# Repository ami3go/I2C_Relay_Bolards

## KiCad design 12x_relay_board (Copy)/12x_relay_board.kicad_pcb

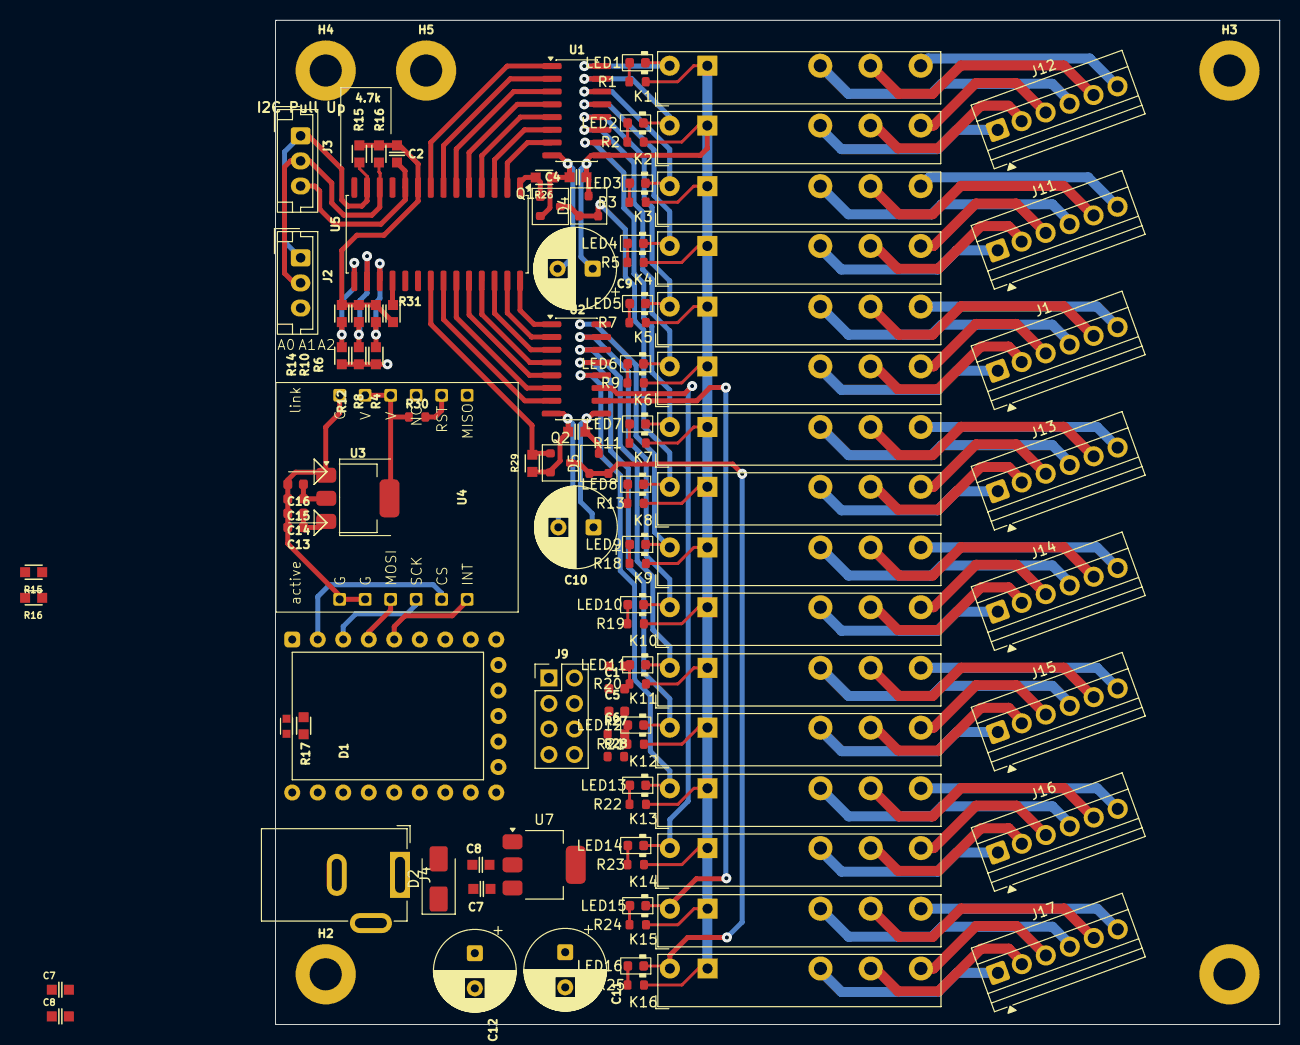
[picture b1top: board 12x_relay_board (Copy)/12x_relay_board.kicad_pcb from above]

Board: 2 copper layers, 100.0 x 100.0 mm, 113 parts (0 on the bottom side), 125 nets.

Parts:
C1, C5, C6, C14, C15: 100nF; C_0603
C2, C3, C4, C7, C7#2, C8, C8#2: 100nF_0603_16V; C_0603
C9, C10, C11, C12: 470uF_25V; CP_Radial_D8.0mm_P3.50mm
C13, C16: 1uF; C_0603
D1: LED_0603
D2: SS14; D_SMA
D4, D5: BAV23C; SOT-23
H1, H2, H3, H4, H5: MountingHole_M3_3.2mm_Pad; MountingHole_3.2mm_Pad
J1, J11, J12, J13, J14, J15, J16, J17: Conn_01x06_Pin; TerminalBlock_Xinya_XY308-2.54-6P_1x06_P2.54mm_Horizontal
J2, J3: JST_03; JST_EH_B3B-EH-A_1x03_P2.50mm_Vertical
J4: Barrel_Jack_Switch; BarrelJack_GCT_DCJ200-10-A_Horizontal
J9: Conn_01x08; PinHeader_2x04_P2.54mm_Vertical
K1, K2, K3, K4, K5, K6, K7, K8, K9, K10, K11, K12, K13, K14, K15, K16: FINDER-34.51; Relay_SPDT_Finder_34.51_Vertical
LED1, LED2, LED3, LED4, LED5, LED6, LED7, LED8, LED9, LED10, LED11, LED12, LED13, LED14, LED15, LED16: LED_0603; LED_0603_1608Metric
Q1, Q2: 2N7002; SOT-23
R1, R2, R3, R5, R7, R9, R11, R13, R18, R19, R20, R21, R22, R23, R24, R25, R27, R28: 4.7kΩ; R_0603
R4, R6, R8, R10, R12, R14, R17, R31: 1k_0603; R_0603
R15, R15#2, R16, R16#2, R26, R29: 10k_0603; R_0603
R30: 10kΩ; R_0603
RZ2: RP2040-Zero; RP2040-Zero_socket
U1, U2: ULN2003; SOIC-16_3.9x9.9mm_P1.27mm
U3, U7: LM1117MP-3.3; SOT-223-3_TabPin2
U4: ENC28J60MODULE; W5500Lite-module
U5: MCP23017_SO; SOIC-28W_7.5x17.9mm_P1.27mm

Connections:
+3V3: C1.1, C6.1, J9.3, R15#2.1, R16.1, R27.1, R28.1, RZ2.21 (3V3)
+5V: C5.1, C13.1, C14.1, J9.2, RZ2.23 (+5V), U3.3 (VI)
/ETH/INT: RZ2.5 (GP4), U4.7 (INT)
/ETH/RST: R30.2, U4.5 (RST)
/Relay_driver1/IN1: U2.1 (I1), U5.28 (GPA7)
/Relay_driver1/IN2: U2.2 (I2), U5.27 (GPA6)
/Relay_driver1/IN3: U2.3 (I3), U5.26 (GPA5)
/Relay_driver1/IN4: U2.4 (I4), U5.25 (GPA4)
/Relay_driver1/IN5: U2.5 (I5), U5.24 (GPA3)
/Relay_driver1/IN6: U2.6 (I6), U5.23 (GPA2)
/Relay_driver1/IN7: U2.7 (I7), U5.22 (GPA1)
/Relay_driver1/IN8: Q2.1 (G), R29.1, U5.21 (GPA0)
/Relay_driver1/OUT1: K9.A2, LED9.1 (K), U2.16 (O1)
/Relay_driver1/OUT2: K10.A2, LED10.1 (K), U2.15 (O2)
/Relay_driver1/OUT3: K11.A2, LED11.1 (K), U2.14 (O3)
/Relay_driver1/OUT4: K12.A2, LED12.1 (K), U2.13 (O4)
/Relay_driver1/OUT5: K13.A2, LED13.1 (K), U2.12 (O5)
/Relay_driver1/OUT6: K14.A2, LED14.1 (K), U2.11 (O6)
/Relay_driver1/OUT7: K15.A2, LED15.1 (K), U2.10 (O7)
/Relay_driver1/OUT8: D5.1 (A2), D5.2 (A1), K16.A2, LED16.1 (K), Q2.3 (D)
/Relay_driver/IN1: U1.1 (I1), U5.8 (GPB7)
/Relay_driver/IN2: U1.2 (I2), U5.7 (GPB6)
/Relay_driver/IN3: U1.3 (I3), U5.6 (GPB5)
/Relay_driver/IN4: U1.4 (I4), U5.5 (GPB4)
/Relay_driver/IN5: U1.5 (I5), U5.4 (GPB3)
/Relay_driver/IN6: U1.6 (I6), U5.3 (GPB2)
/Relay_driver/IN7: U1.7 (I7), U5.2 (GPB1)
/Relay_driver/IN8: Q1.1 (G), R26.1, U5.1 (GPB0)
/Relay_driver/OUT1: K1.A2, LED1.1 (K), U1.16 (O1)
/Relay_driver/OUT2: K2.A2, LED2.1 (K), U1.15 (O2)
/Relay_driver/OUT3: K3.A2, LED3.1 (K), U1.14 (O3)
/Relay_driver/OUT4: K4.A2, LED4.1 (K), U1.13 (O4)
/Relay_driver/OUT5: K5.A2, LED5.1 (K), U1.12 (O5)
/Relay_driver/OUT6: K6.A2, LED6.1 (K), U1.11 (O6)
/Relay_driver/OUT7: K7.A2, LED7.1 (K), U1.10 (O7)
/Relay_driver/OUT8: D4.1 (A2), D4.2 (A1), K8.A2, LED8.1 (K), Q1.3 (D)
/Two_relays_1/Relay_channel_1/COM: J12.5, K1.11
/Two_relays_1/Relay_channel_1/NC: J12.4, K1.12
/Two_relays_1/Relay_channel_1/NO: J12.6, K1.14
/Two_relays_1/Relay_channel_2/COM: J12.2, K2.11
/Two_relays_1/Relay_channel_2/NC: J12.1, K2.12
/Two_relays_1/Relay_channel_2/NO: J12.3, K2.14
/Two_relays_2/Relay_channel_1/COM: J11.5, K3.11
/Two_relays_2/Relay_channel_1/NC: J11.4, K3.12
/Two_relays_2/Relay_channel_1/NO: J11.6, K3.14
/Two_relays_2/Relay_channel_2/COM: J11.2, K4.11
/Two_relays_2/Relay_channel_2/NC: J11.1, K4.12
/Two_relays_2/Relay_channel_2/NO: J11.3, K4.14
/Two_relays_3/Relay_channel_1/COM: J1.5, K5.11
/Two_relays_3/Relay_channel_1/NC: J1.4, K5.12
/Two_relays_3/Relay_channel_1/NO: J1.6, K5.14
/Two_relays_3/Relay_channel_2/COM: J1.2, K6.11
/Two_relays_3/Relay_channel_2/NC: J1.1, K6.12
/Two_relays_3/Relay_channel_2/NO: J1.3, K6.14
/Two_relays_4/Relay_channel_1/COM: J13.5, K7.11
/Two_relays_4/Relay_channel_1/NC: J13.4, K7.12
/Two_relays_4/Relay_channel_1/NO: J13.6, K7.14
/Two_relays_4/Relay_channel_2/COM: J13.2, K8.11
/Two_relays_4/Relay_channel_2/NC: J13.1, K8.12
/Two_relays_4/Relay_channel_2/NO: J13.3, K8.14
/Two_relays_5/Relay_channel_1/COM: J14.5, K9.11
/Two_relays_5/Relay_channel_1/NC: J14.4, K9.12
/Two_relays_5/Relay_channel_1/NO: J14.6, K9.14
/Two_relays_5/Relay_channel_2/COM: J14.2, K10.11
/Two_relays_5/Relay_channel_2/NC: J14.1, K10.12
/Two_relays_5/Relay_channel_2/NO: J14.3, K10.14
/Two_relays_6/Relay_channel_1/COM: J15.5, K11.11
/Two_relays_6/Relay_channel_1/NC: J15.4, K11.12
/Two_relays_6/Relay_channel_1/NO: J15.6, K11.14
/Two_relays_6/Relay_channel_2/COM: J15.2, K12.11
/Two_relays_6/Relay_channel_2/NC: J15.1, K12.12
/Two_relays_6/Relay_channel_2/NO: J15.3, K12.14
/Two_relays_7/Relay_channel_1/COM: J16.5, K13.11
/Two_relays_7/Relay_channel_1/NC: J16.4, K13.12
/Two_relays_7/Relay_channel_1/NO: J16.6, K13.14
/Two_relays_7/Relay_channel_2/COM: J16.2, K14.11
/Two_relays_7/Relay_channel_2/NC: J16.1, K14.12
/Two_relays_7/Relay_channel_2/NO: J16.3, K14.14
/Two_relays_8/Relay_channel_1/COM: J17.5, K15.11
/Two_relays_8/Relay_channel_1/NC: J17.4, K15.12
/Two_relays_8/Relay_channel_1/NO: J17.6, K15.14
/Two_relays_8/Relay_channel_2/COM: J17.2, K16.11
/Two_relays_8/Relay_channel_2/NC: J17.1, K16.12
/Two_relays_8/Relay_channel_2/NO: J17.3, K16.14
/Untitled Sheet/I2C0_SCL: R16.2, RZ2.14 (GP13)
/Untitled Sheet/I2C0_SDA: R15#2.2, RZ2.13 (GP12)
/Untitled Sheet/I2C1_SCL: J9.5, R27.2, RZ2.18 (GP27)
/Untitled Sheet/I2C1_SDA: J9.7, R28.2, RZ2.17 (GP26)
/Untitled Sheet/SPI0_CS: RZ2.2 (GP1), U4.8 (CS)
/Untitled Sheet/SPI0_MOSI: RZ2.4 (GP3), U4.10 (MOSI)
/Untitled Sheet/SPI0_RX: RZ2.1 (GP0), U4.6 (MISO)
/Untitled Sheet/SPI0_SCK: RZ2.3 (GP2), U4.9 (SCK)
/conrol/PWR_VDD: C2.1, R4.1, R8.1, R12.1, R31.1, U5.9 (VDD)
/conrol/SCL: J2.2, J3.2, R16#2.2, U5.12 (SCK)
/conrol/SDA: J2.1, J3.1, R15.2, U5.13 (SDA)
GND: C1.2, C5.2, C6.2, C13.2, C14.2, C15.2, C16.2, J9.1, J9.8, RZ2.22 (GND), U3.1 (GND), U4.1 (G), U4.11 (GND), U4.12 (GND)
unnamed: D1.2 (A), R17.2
unnamed: D2.2 (A), J4.1
unnamed: J9.4, RZ2.20 (GP29)
unnamed: J9.6, RZ2.19 (GP28)
unnamed: LED1.2 (A), R1.2
unnamed: LED2.2 (A), R2.2
unnamed: LED3.2 (A), R3.2
unnamed: LED4.2 (A), R5.2
unnamed: LED5.2 (A), R7.2
unnamed: LED6.2 (A), R9.2
unnamed: LED7.2 (A), R11.2
unnamed: LED8.2 (A), R13.2
unnamed: LED9.2 (A), R18.2
unnamed: LED10.2 (A), R19.2
unnamed: LED11.2 (A), R20.2
unnamed: LED12.2 (A), R21.2
unnamed: LED13.2 (A), R22.2
unnamed: LED14.2 (A), R23.2
unnamed: LED15.2 (A), R24.2
unnamed: LED16.2 (A), R25.2
unnamed: C15.1, C16.1, R30.1, U3.2 (VO), U4.2 (P3V3), U4.3 (P3V3)
unnamed: R12.2, R14.1, U5.15 (A0)
unnamed: R8.2, R10.1, U5.16 (A1)
unnamed: R4.2, R6.1, U5.17 (A2)
unnamed: R31.2, U5.18 (~RESET)
PWR_3V3: C8.1, U7.2 (VO)
PWR_5V: C8#2.1, R15.1, R16#2.1
PWR_12V: C3.1, C4.1, C7.1, C7#2.1, C9.1, C10.1, C11.1, C12.1, D2.1 (K), D4.3 (K), D5.3 (K), K1.A1, K2.A1, K3.A1, K4.A1, K5.A1, K6.A1, K7.A1, K8.A1, K9.A1, K10.A1, K11.A1, K12.A1, K13.A1, K14.A1, K15.A1, K16.A1, R1.1, R2.1, R3.1, R5.1, R7.1, R9.1, R11.1, R13.1, R17.1, R18.1, R19.1, R20.1, R21.1, R22.1, R23.1, R24.1, R25.1, U1.9 (COM), U2.9 (COM), U7.3 (VI)
PWR_GND: C2.2, C3.2, C4.2, C7.2, C7#2.2, C8.2, C8#2.2, C9.2, C10.2, C11.2, C12.2, D1.1 (K), J2.3, J3.3, J4.2, J4.3, Q1.2 (S), Q2.2 (S), R6.2, R10.2, R14.2, R26.2, R29.2, U1.8 (GND), U2.8 (GND), U5.10 (VSS), U7.1 (GND)

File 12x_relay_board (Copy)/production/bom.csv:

Designator,Footprint,Quantity,Value,LCSC Part #
"C10, C11, C12, C9",CP_Radial_D8.0mm_P3.50mm,4,470uF_25V,
"C2, C3, C4, C7, C8",C_0603,5,100nF_0603_16V,
D1,LED_0603,1,LED_0603,
D2,D_SMA,1,SS14,
"H1, H2, H3, H4, H5",MountingHole_3.2mm_Pad,5,MountingHole_M3_3.2mm_Pad,
J1,PinHeader_1x36_P2.54mm_Vertical,1,Conn_01x36_MountingPin,
"J2, J3",JST_EH_B3B-EH-A_1x03_P2.50mm_Vertical,2,JST_03,
J4,BarrelJack_GCT_DCJ200-10-A_Horizontal,1,Barrel_Jack_Switch,
"K1, K10, K11, K12, K2, K3, K4, K5, K6, K7, K8, K9",Relay_SPDT_Finder_34.51_Vertical,12,FINDER-34.51,
"R10, R12, R14, R17, R2, R4, R6, R8",R_0603,8,1k_0603,
"R15, R16",R_0603,2,10k_0603,
"U1, U2",SOIC-16_3.9x9.9mm_P1.27mm,2,ULN2003,
U5,SOIC-28W_7.5x17.9mm_P1.27mm,1,MCP23017_SO,
U7,SOT-223-3_TabPin2,1,LM1117MP-3.3,

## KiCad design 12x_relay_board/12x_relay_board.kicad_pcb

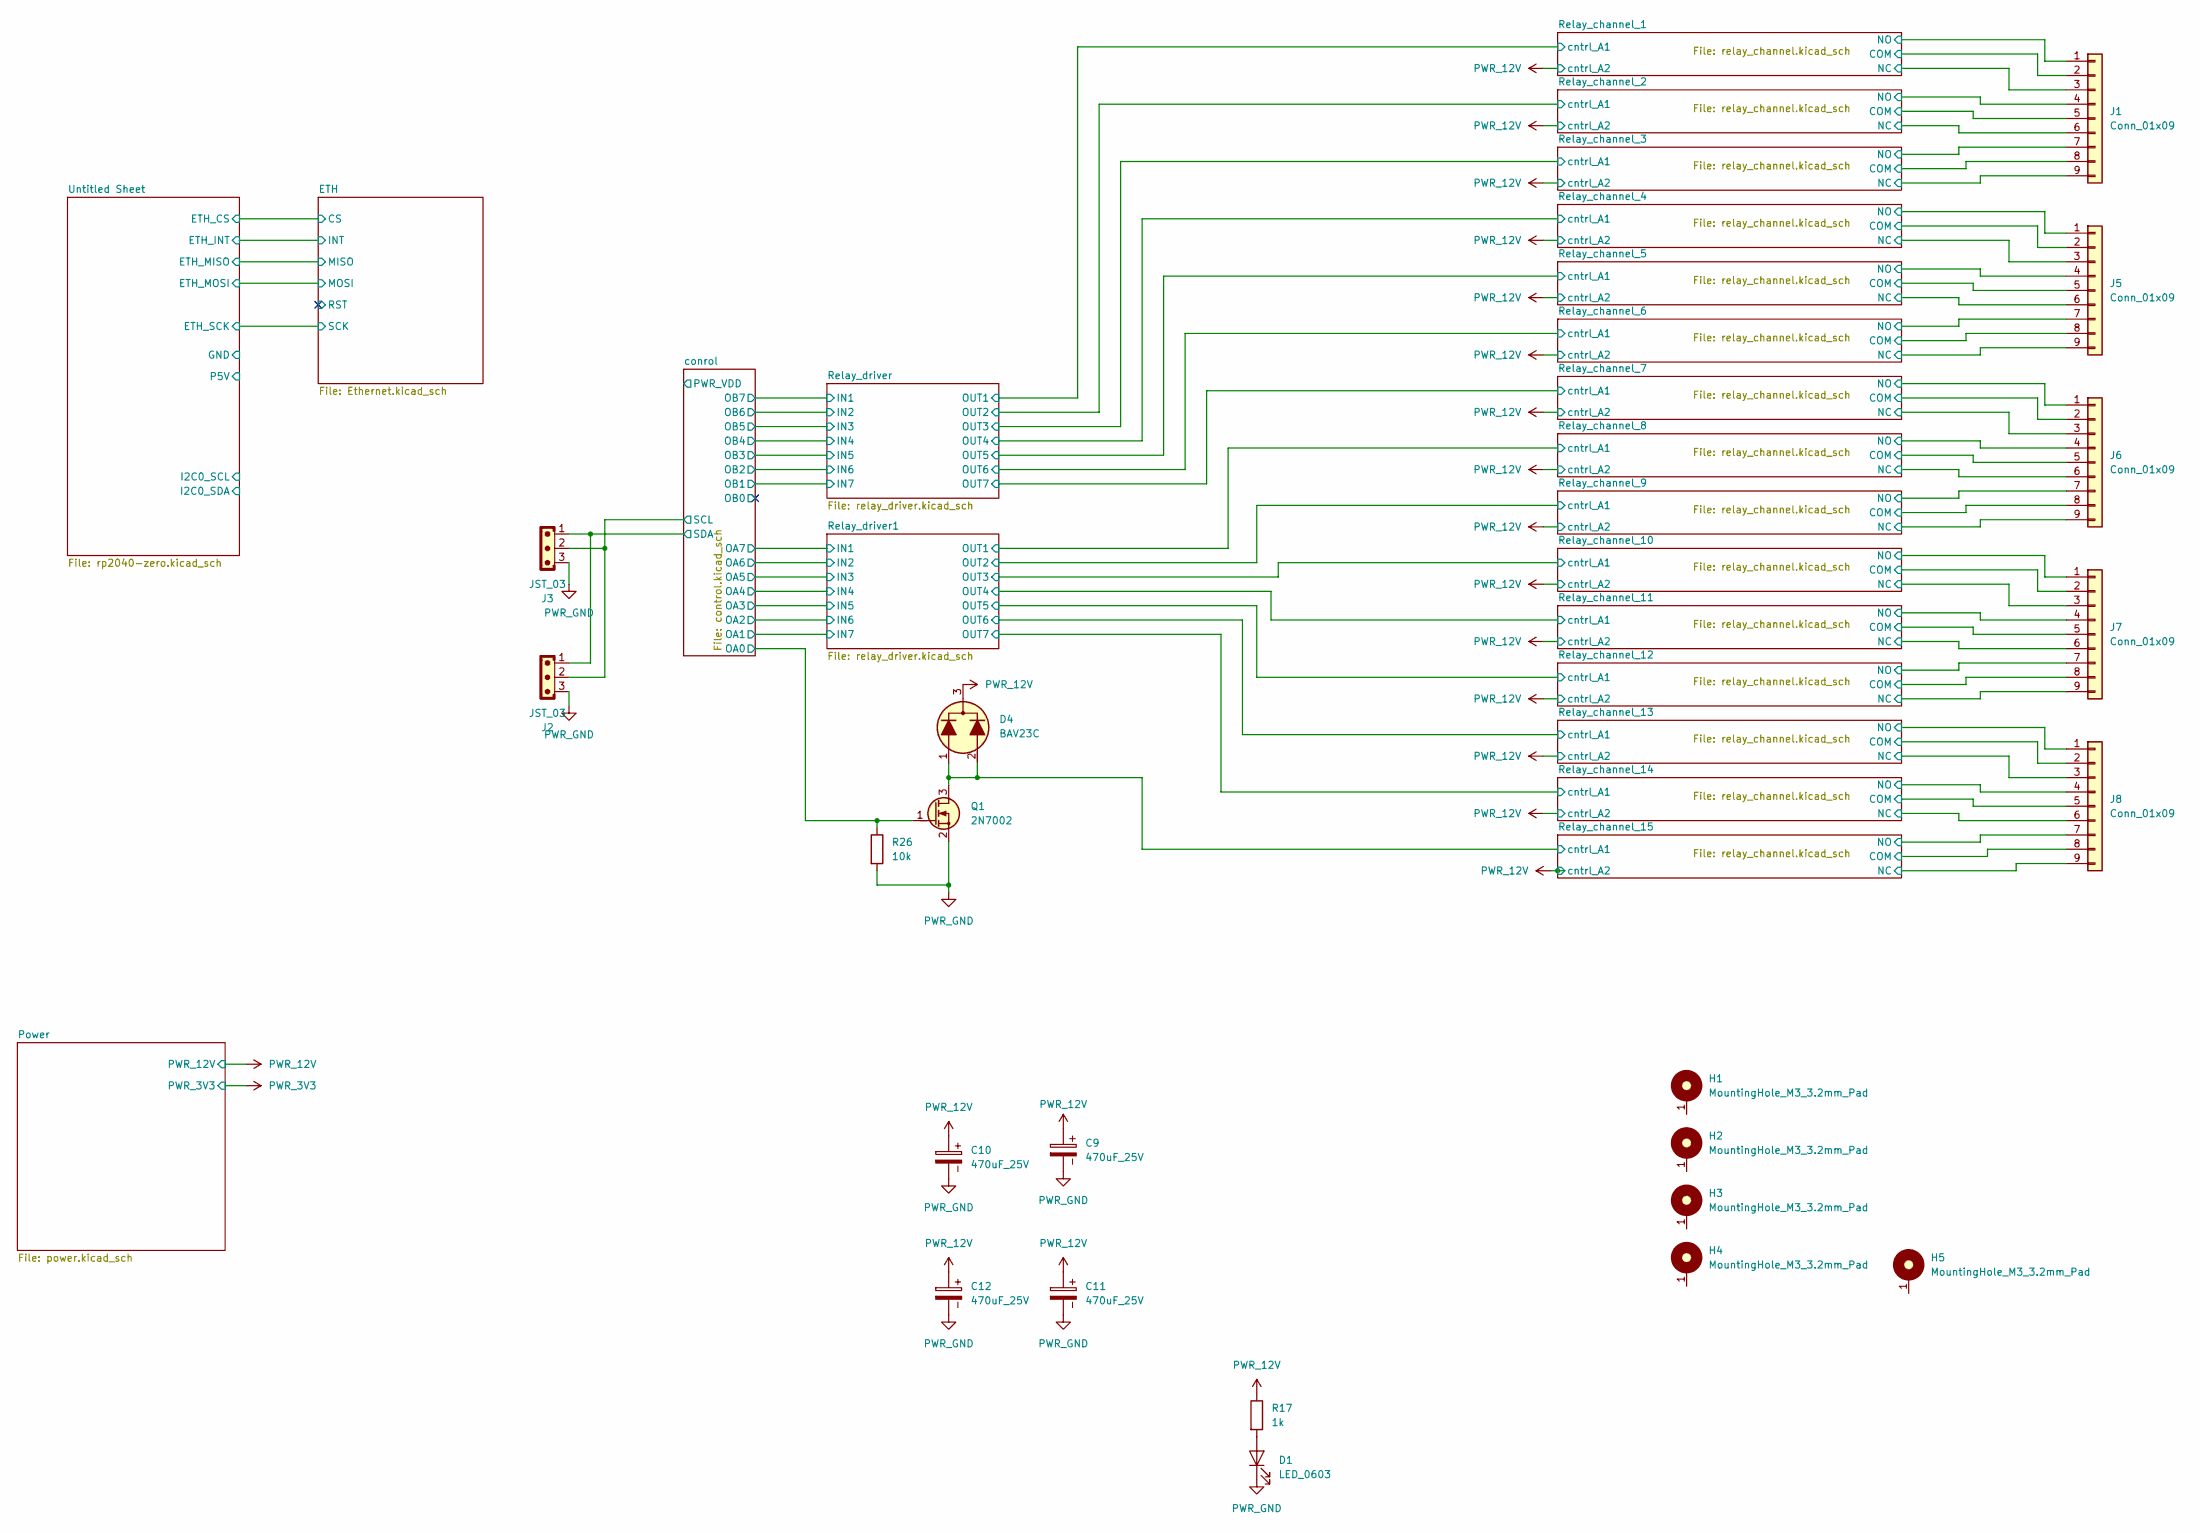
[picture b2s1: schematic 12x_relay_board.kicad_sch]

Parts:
C9, C10, C11, C12: 470uF_25V; CP_Radial_D8.0mm_P3.50mm
D1: LED_0603
D4: BAV23C; SOT-23
H1, H2, H3, H4, H5: MountingHole_M3_3.2mm_Pad; MountingHole_3.2mm_Pad
J1, J5, J6, J7, J8: Conn_01x09; TerminalBlock_Xinya_XY308-2.54-9P_1x09_P2.54mm_Horizontal
J2, J3: JST_03; JST_EH_B3B-EH-A_1x03_P2.50mm_Vertical
Q1: 2N7002; SOT-23
R17: 1k_0603; R_0603; Part Number RC0603FR-071KL; JLCPCB ID C21190
R26: 10k_0603; R_0603; Part Number RC0603FR-0710KL; JLCPCB ID C25804

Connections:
/Relay_channel_1/COM: J1.2; also elsewhere on the board
/Relay_channel_1/NC: J1.3; also elsewhere on the board
/Relay_channel_1/NO: J1.1; also elsewhere on the board
/Relay_channel_2/COM: J1.5; also elsewhere on the board
/Relay_channel_2/NC: J1.6; also elsewhere on the board
/Relay_channel_2/NO: J1.4; also elsewhere on the board
/Relay_channel_3/COM: J1.8; also elsewhere on the board
/Relay_channel_3/NC: J1.9; also elsewhere on the board
/Relay_channel_3/NO: J1.7; also elsewhere on the board
/Relay_channel_4/COM: J5.2; also elsewhere on the board
/Relay_channel_4/NC: J5.3; also elsewhere on the board
/Relay_channel_4/NO: J5.1; also elsewhere on the board
/Relay_channel_5/COM: J5.5; also elsewhere on the board
/Relay_channel_5/NC: J5.6; also elsewhere on the board
/Relay_channel_5/NO: J5.4; also elsewhere on the board
/Relay_channel_6/COM: J5.8; also elsewhere on the board
/Relay_channel_6/NC: J5.9; also elsewhere on the board
/Relay_channel_6/NO: J5.7; also elsewhere on the board
/Relay_channel_7/COM: J6.2; also elsewhere on the board
/Relay_channel_7/NC: J6.3; also elsewhere on the board
/Relay_channel_7/NO: J6.1; also elsewhere on the board
/Relay_channel_8/COM: J6.5; also elsewhere on the board
/Relay_channel_8/NC: J6.6; also elsewhere on the board
/Relay_channel_8/NO: J6.4; also elsewhere on the board
/Relay_channel_9/COM: J6.8; also elsewhere on the board
/Relay_channel_9/NC: J6.9; also elsewhere on the board
/Relay_channel_9/NO: J6.7; also elsewhere on the board
/Relay_channel_10/COM: J7.2; also elsewhere on the board
/Relay_channel_10/NC: J7.3; also elsewhere on the board
/Relay_channel_10/NO: J7.1; also elsewhere on the board
/Relay_channel_11/COM: J7.5; also elsewhere on the board
/Relay_channel_11/NC: J7.6; also elsewhere on the board
/Relay_channel_11/NO: J7.4; also elsewhere on the board
/Relay_channel_12/COM: J7.8; also elsewhere on the board
/Relay_channel_12/NC: J7.9; also elsewhere on the board
/Relay_channel_12/NO: J7.7; also elsewhere on the board
/Relay_channel_13/COM: J8.2; also elsewhere on the board
/Relay_channel_13/NC: J8.3; also elsewhere on the board
/Relay_channel_13/NO: J8.1; also elsewhere on the board
/Relay_channel_14/COM: J8.5; also elsewhere on the board
/Relay_channel_14/NC: J8.6; also elsewhere on the board
/Relay_channel_14/NO: J8.4; also elsewhere on the board
/Relay_channel_15/COM: J8.8; also elsewhere on the board
/Relay_channel_15/NC: J8.9; also elsewhere on the board
/Relay_channel_15/NO: J8.7; also elsewhere on the board
/Relay_channel_15/cntrl_A1: D4.1 (A2), D4.2 (A1), Q1.3 (D); also elsewhere on the board
/conrol/OA0: Q1.1 (G), R26.1; also elsewhere on the board
/conrol/SCL: J2.2, J3.2; also elsewhere on the board
/conrol/SDA: J2.1, J3.1; also elsewhere on the board
unnamed: D1.2 (A), R17.2
PWR_12V: C9.1, C10.1, C11.1, C12.1, D4.3 (K), R17.1; also elsewhere on the board
PWR_GND: C9.2, C10.2, C11.2, C12.2, D1.1 (K), J2.3, J3.3, Q1.2 (S), R26.2; also elsewhere on the board

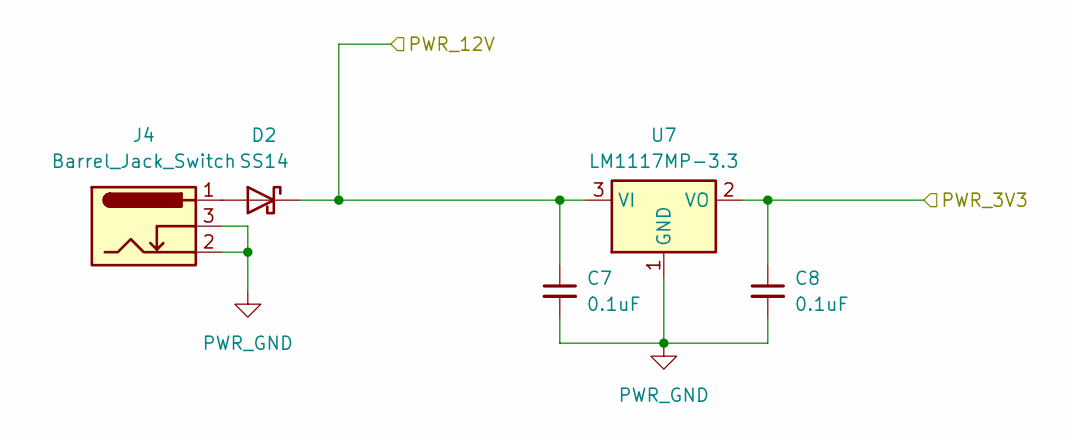
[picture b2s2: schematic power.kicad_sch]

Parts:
C7, C8: 100nF_0603_16V; C_0603; Part Number 0603YC104KAT2A; JLCPCB ID C14663
D2: SS14; D_SMA
J4: Barrel_Jack_Switch; BarrelJack_GCT_DCJ200-10-A_Horizontal
U7: LM1117MP-3.3; SOT-223-3_TabPin2

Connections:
unnamed: D2.2 (A), J4.1
PWR_12V: C7.1, D2.1 (K), U7.3 (VI); also elsewhere on the board
PWR_GND: C7.2, C8.2, J4.2, J4.3, U7.1 (GND); also elsewhere on the board

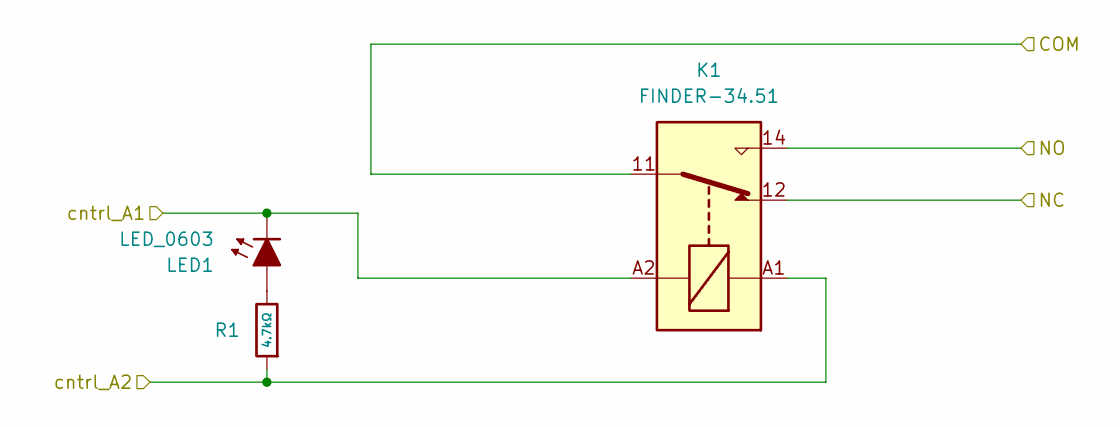
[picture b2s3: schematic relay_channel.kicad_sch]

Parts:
K1: FINDER-34.51; Relay_SPDT_Finder_34.51_Vertical
LED1: LED_0603; LED_0603_1608Metric
R1: 4.7kΩ; R_0603; Overload Voltage (Max) 75V; Tolerance ±1%; Part 0603WAF4701T5E; LCSC C23162

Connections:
/Relay_channel_1/COM: K1.11; also elsewhere on the board
/Relay_channel_1/NC: K1.12; also elsewhere on the board
/Relay_channel_1/NO: K1.14; also elsewhere on the board
/Relay_channel_1/cntrl_A1: K1.A2, LED1.1 (K); also elsewhere on the board
unnamed: LED1.2 (A), R1.2
PWR_12V: K1.A1, R1.1; also elsewhere on the board

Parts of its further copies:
K2, K3, K4, K5, K6, K7, K8, K9, K10, K11, K12, K13, K14, K15: FINDER-34.51; Relay_SPDT_Finder_34.51_Vertical
LED2, LED3, LED4, LED5, LED6, LED7, LED8, LED9, LED10, LED11, LED12, LED13, LED14, LED15: LED_0603; LED_0603_1608Metric
R3, R5, R7, R9, R11, R13, R18, R19, R20, R21, R22, R23, R24, R25: 4.7kΩ; R_0603; Overload Voltage (Max) 75V; Tolerance ±1%; Part 0603WAF4701T5E; LCSC C23162

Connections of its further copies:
/Relay_channel_2/COM: K2.11; also elsewhere on the board
/Relay_channel_2/NC: K2.12; also elsewhere on the board
/Relay_channel_2/NO: K2.14; also elsewhere on the board
/Relay_channel_2/cntrl_A1: K2.A2, LED2.1 (K); also elsewhere on the board
/Relay_channel_3/COM: K3.11; also elsewhere on the board
/Relay_channel_3/NC: K3.12; also elsewhere on the board
/Relay_channel_3/NO: K3.14; also elsewhere on the board
/Relay_channel_3/cntrl_A1: K3.A2, LED3.1 (K); also elsewhere on the board
/Relay_channel_4/COM: K4.11; also elsewhere on the board
/Relay_channel_4/NC: K4.12; also elsewhere on the board
/Relay_channel_4/NO: K4.14; also elsewhere on the board
/Relay_channel_4/cntrl_A1: K4.A2, LED4.1 (K); also elsewhere on the board
/Relay_channel_5/COM: K5.11; also elsewhere on the board
/Relay_channel_5/NC: K5.12; also elsewhere on the board
/Relay_channel_5/NO: K5.14; also elsewhere on the board
/Relay_channel_5/cntrl_A1: K5.A2, LED5.1 (K); also elsewhere on the board
/Relay_channel_6/COM: K6.11; also elsewhere on the board
/Relay_channel_6/NC: K6.12; also elsewhere on the board
/Relay_channel_6/NO: K6.14; also elsewhere on the board
/Relay_channel_6/cntrl_A1: K6.A2, LED6.1 (K); also elsewhere on the board
/Relay_channel_7/COM: K7.11; also elsewhere on the board
/Relay_channel_7/NC: K7.12; also elsewhere on the board
/Relay_channel_7/NO: K7.14; also elsewhere on the board
/Relay_channel_7/cntrl_A1: K7.A2, LED7.1 (K); also elsewhere on the board
/Relay_channel_8/COM: K8.11; also elsewhere on the board
/Relay_channel_8/NC: K8.12; also elsewhere on the board
/Relay_channel_8/NO: K8.14; also elsewhere on the board
/Relay_channel_8/cntrl_A1: K8.A2, LED8.1 (K); also elsewhere on the board
/Relay_channel_9/COM: K9.11; also elsewhere on the board
/Relay_channel_9/NC: K9.12; also elsewhere on the board
/Relay_channel_9/NO: K9.14; also elsewhere on the board
/Relay_channel_9/cntrl_A1: K9.A2, LED9.1 (K); also elsewhere on the board
/Relay_channel_10/COM: K10.11; also elsewhere on the board
/Relay_channel_10/NC: K10.12; also elsewhere on the board
/Relay_channel_10/NO: K10.14; also elsewhere on the board
/Relay_channel_10/cntrl_A1: K10.A2, LED10.1 (K); also elsewhere on the board
/Relay_channel_11/COM: K11.11; also elsewhere on the board
/Relay_channel_11/NC: K11.12; also elsewhere on the board
/Relay_channel_11/NO: K11.14; also elsewhere on the board
/Relay_channel_11/cntrl_A1: K11.A2, LED11.1 (K); also elsewhere on the board
/Relay_channel_12/COM: K12.11; also elsewhere on the board
/Relay_channel_12/NC: K12.12; also elsewhere on the board
/Relay_channel_12/NO: K12.14; also elsewhere on the board
/Relay_channel_12/cntrl_A1: K12.A2, LED12.1 (K); also elsewhere on the board
/Relay_channel_13/COM: K13.11; also elsewhere on the board
/Relay_channel_13/NC: K13.12; also elsewhere on the board
/Relay_channel_13/NO: K13.14; also elsewhere on the board
/Relay_channel_13/cntrl_A1: K13.A2, LED13.1 (K); also elsewhere on the board
/Relay_channel_14/COM: K14.11; also elsewhere on the board
/Relay_channel_14/NC: K14.12; also elsewhere on the board
/Relay_channel_14/NO: K14.14; also elsewhere on the board
/Relay_channel_14/cntrl_A1: K14.A2, LED14.1 (K); also elsewhere on the board
/Relay_channel_15/COM: K15.11; also elsewhere on the board
/Relay_channel_15/NC: K15.12; also elsewhere on the board
/Relay_channel_15/NO: K15.14; also elsewhere on the board
/Relay_channel_15/cntrl_A1: K15.A2, LED15.1 (K); also elsewhere on the board
unnamed: LED2.2 (A), R3.2
unnamed: LED3.2 (A), R5.2
unnamed: LED4.2 (A), R7.2
unnamed: LED5.2 (A), R9.2
unnamed: LED6.2 (A), R11.2
unnamed: LED7.2 (A), R13.2
unnamed: LED8.2 (A), R18.2
unnamed: LED9.2 (A), R19.2
unnamed: LED10.2 (A), R20.2
unnamed: LED11.2 (A), R21.2
unnamed: LED12.2 (A), R22.2
unnamed: LED13.2 (A), R23.2
unnamed: LED14.2 (A), R24.2
unnamed: LED15.2 (A), R25.2
PWR_12V: K2.A1, K3.A1, K4.A1, K5.A1, K6.A1, K7.A1, K8.A1, K9.A1, K10.A1, K11.A1, K12.A1, K13.A1, K14.A1, K15.A1, R3.1, R5.1, R7.1, R9.1, R11.1, R13.1, R18.1, R19.1, R20.1, R21.1, R22.1, R23.1, R24.1, R25.1; also elsewhere on the board

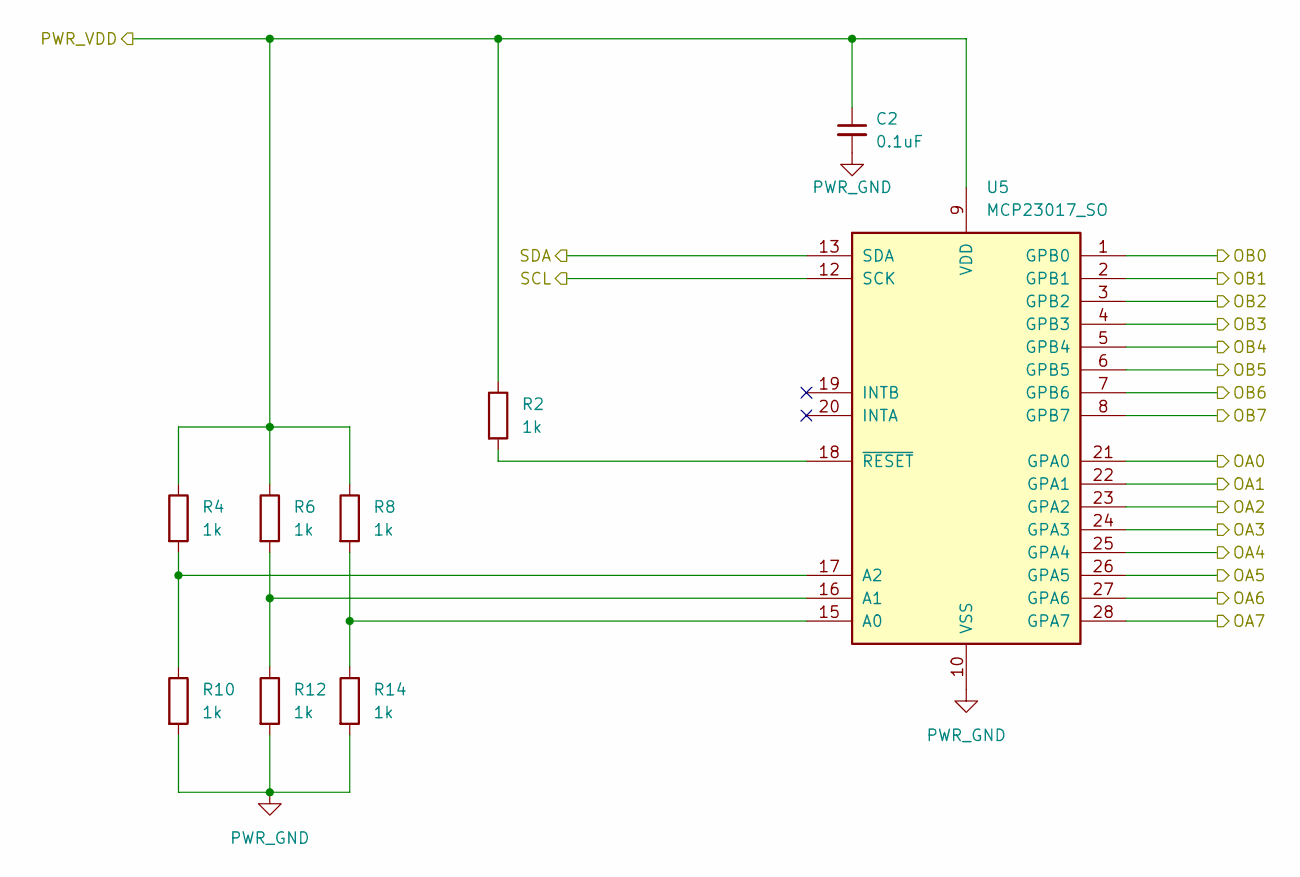
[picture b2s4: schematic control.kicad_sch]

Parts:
C2: 100nF_0603_16V; C_0603; Part Number 0603YC104KAT2A; JLCPCB ID C14663
R2, R4, R6, R8, R10, R12, R14: 1k_0603; R_0603; Part Number RC0603FR-071KL; JLCPCB ID C21190
U5: MCP23017_SO; SOIC-28W_7.5x17.9mm_P1.27mm

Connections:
/Relay_driver1/IN1: U5.28 (GPA7); also elsewhere on the board
/Relay_driver1/IN2: U5.27 (GPA6); also elsewhere on the board
/Relay_driver1/IN3: U5.26 (GPA5); also elsewhere on the board
/Relay_driver1/IN4: U5.25 (GPA4); also elsewhere on the board
/Relay_driver1/IN5: U5.24 (GPA3); also elsewhere on the board
/Relay_driver1/IN6: U5.23 (GPA2); also elsewhere on the board
/Relay_driver1/IN7: U5.22 (GPA1); also elsewhere on the board
/Relay_driver/IN1: U5.8 (GPB7); also elsewhere on the board
/Relay_driver/IN2: U5.7 (GPB6); also elsewhere on the board
/Relay_driver/IN3: U5.6 (GPB5); also elsewhere on the board
/Relay_driver/IN4: U5.5 (GPB4); also elsewhere on the board
/Relay_driver/IN5: U5.4 (GPB3); also elsewhere on the board
/Relay_driver/IN6: U5.3 (GPB2); also elsewhere on the board
/Relay_driver/IN7: U5.2 (GPB1); also elsewhere on the board
/conrol/OA0: U5.21 (GPA0); also elsewhere on the board
/conrol/OB0: U5.1 (GPB0)
/conrol/SCL: U5.12 (SCK); also elsewhere on the board
/conrol/SDA: U5.13 (SDA); also elsewhere on the board
unnamed: R8.2, R14.1, U5.15 (A0)
unnamed: R6.2, R12.1, U5.16 (A1)
unnamed: R4.2, R10.1, U5.17 (A2)
unnamed: R2.2, U5.18 (~RESET)
PWR_GND: C2.2, R10.2, R12.2, R14.2, U5.10 (VSS); also elsewhere on the board

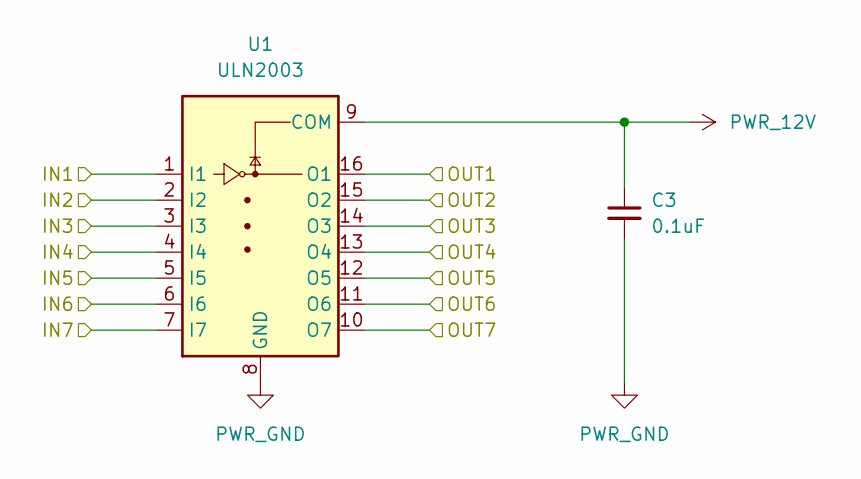
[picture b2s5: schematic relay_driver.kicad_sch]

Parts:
C3: 100nF_0603_16V; C_0603; Part Number 0603YC104KAT2A; JLCPCB ID C14663
U1: ULN2003; SOIC-16_3.9x9.9mm_P1.27mm

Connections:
/Relay_channel_1/cntrl_A1: U1.16 (O1); also elsewhere on the board
/Relay_channel_2/cntrl_A1: U1.15 (O2); also elsewhere on the board
/Relay_channel_3/cntrl_A1: U1.14 (O3); also elsewhere on the board
/Relay_channel_4/cntrl_A1: U1.13 (O4); also elsewhere on the board
/Relay_channel_5/cntrl_A1: U1.12 (O5); also elsewhere on the board
/Relay_channel_6/cntrl_A1: U1.11 (O6); also elsewhere on the board
/Relay_channel_7/cntrl_A1: U1.10 (O7); also elsewhere on the board
/Relay_driver/IN1: U1.1 (I1); also elsewhere on the board
/Relay_driver/IN2: U1.2 (I2); also elsewhere on the board
/Relay_driver/IN3: U1.3 (I3); also elsewhere on the board
/Relay_driver/IN4: U1.4 (I4); also elsewhere on the board
/Relay_driver/IN5: U1.5 (I5); also elsewhere on the board
/Relay_driver/IN6: U1.6 (I6); also elsewhere on the board
/Relay_driver/IN7: U1.7 (I7); also elsewhere on the board
PWR_12V: C3.1, U1.9 (COM); also elsewhere on the board
PWR_GND: C3.2, U1.8 (GND); also elsewhere on the board

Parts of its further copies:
C4: 100nF_0603_16V; C_0603; Part Number 0603YC104KAT2A; JLCPCB ID C14663
U2: ULN2003; SOIC-16_3.9x9.9mm_P1.27mm

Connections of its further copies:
/Relay_channel_8/cntrl_A1: U2.16 (O1); also elsewhere on the board
/Relay_channel_9/cntrl_A1: U2.15 (O2); also elsewhere on the board
/Relay_channel_10/cntrl_A1: U2.14 (O3); also elsewhere on the board
/Relay_channel_11/cntrl_A1: U2.13 (O4); also elsewhere on the board
/Relay_channel_12/cntrl_A1: U2.12 (O5); also elsewhere on the board
/Relay_channel_13/cntrl_A1: U2.11 (O6); also elsewhere on the board
/Relay_channel_14/cntrl_A1: U2.10 (O7); also elsewhere on the board
/Relay_driver1/IN1: U2.1 (I1); also elsewhere on the board
/Relay_driver1/IN2: U2.2 (I2); also elsewhere on the board
/Relay_driver1/IN3: U2.3 (I3); also elsewhere on the board
/Relay_driver1/IN4: U2.4 (I4); also elsewhere on the board
/Relay_driver1/IN5: U2.5 (I5); also elsewhere on the board
/Relay_driver1/IN6: U2.6 (I6); also elsewhere on the board
/Relay_driver1/IN7: U2.7 (I7); also elsewhere on the board
PWR_12V: C4.1, U2.9 (COM); also elsewhere on the board
PWR_GND: C4.2, U2.8 (GND); also elsewhere on the board

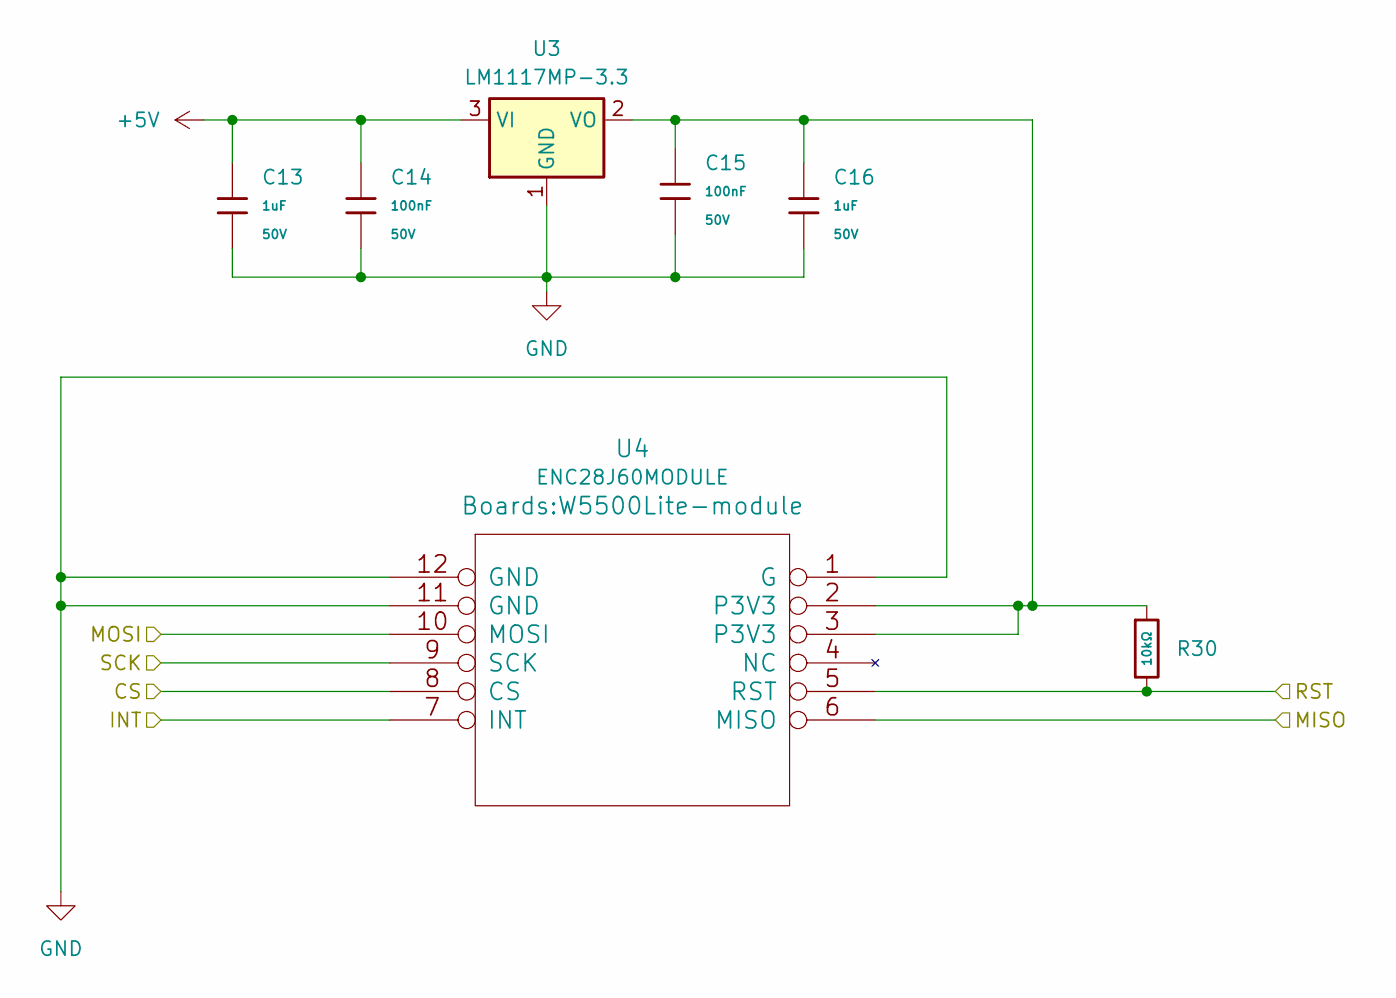
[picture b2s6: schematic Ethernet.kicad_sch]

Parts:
C13, C16: 1uF; C_0603; Tolerance ±10%; Voltage Rated 50V; Part CL10A105KB8NNNC; LCSC C15849
C14, C15: 100nF; C_0603; Voltage Rated 50V; Tolerance ±10%; Part CC0603KRX7R9BB104; LCSC C14663
R30: 10kΩ; R_0603; Overload Voltage (Max) 75V; Tolerance ±1%; Part 0603WAF1002T5E; LCSC C25804
U3: LM1117MP-3.3; SOT-223-3_TabPin2; LCSC Part # C498153
U4: ENC28J60MODULE; W5500Lite-module

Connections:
+5V: C13.1, C14.1, U3.3 (VI); also elsewhere on the board
/ETH/INT: U4.7 (INT); also elsewhere on the board
/ETH/RST: R30.2, U4.5 (RST)
/Untitled Sheet/SPI0_CS: U4.8 (CS); also elsewhere on the board
/Untitled Sheet/SPI0_MOSI: U4.10 (MOSI); also elsewhere on the board
/Untitled Sheet/SPI0_RX: U4.6 (MISO); also elsewhere on the board
/Untitled Sheet/SPI0_SCK: U4.9 (SCK); also elsewhere on the board
GND: C13.2, C14.2, C15.2, C16.2, U3.1 (GND), U4.1 (G), U4.11 (GND), U4.12 (GND); also elsewhere on the board
unnamed: C15.1, C16.1, R30.1, U3.2 (VO), U4.2 (P3V3), U4.3 (P3V3)
